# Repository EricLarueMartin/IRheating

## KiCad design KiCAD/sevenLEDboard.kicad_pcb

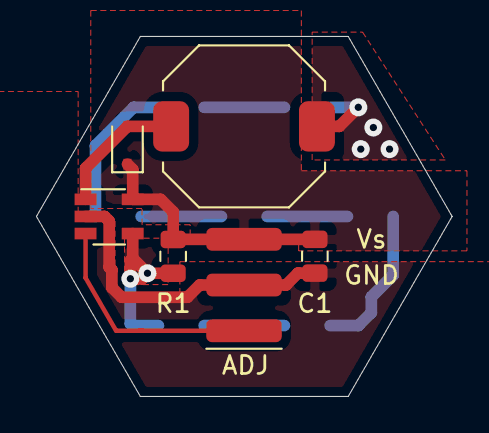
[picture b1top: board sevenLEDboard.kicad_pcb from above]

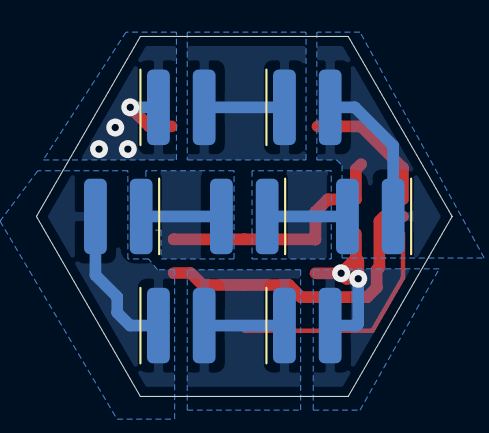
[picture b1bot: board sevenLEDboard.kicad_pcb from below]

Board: 2 copper layers, 23.1 x 20.0 mm, 13 parts (7 on the bottom side), 12 nets.

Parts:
C1: 10uF; C_0805_2012Metric
D1, D2, D3, D4, D5, D6, D7: SFH 4550; 91601-302LF
D8: D_Schottky; D_SOD-323
J1: Conn_01x03_Male; 91601-303LF
L1: 68uH; CDRH8D58
R1: 1; R_0805_2012Metric
U1: ZXLD1350; TSOT-23-5

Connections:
GND: C1.2, J1.2, U1.2
unnamed: D1.1, D2.2
unnamed: D1.2, R1.1, U1.4
unnamed: D2.1, D3.2
unnamed: D3.1, D4.2
unnamed: D4.1, D5.2
unnamed: D5.1, D6.2
unnamed: D6.1, D7.2
unnamed: D7.1, L1.1
unnamed: D8.2, L1.2, U1.1
unnamed: J1.1, U1.3
VS: C1.1, D8.1, J1.3, R1.2, U1.5

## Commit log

2021-11-10 Data sheets and model for some selected components.
2021-11-11 Design and layout of 7 LED board.
2021-11-11 Updated board. Draft for review before PCB submission.
2021-11-12 Final changes with fabrication outputs.
2021-11-12 Created production 7 LED board with ZXLD1350 DC-DC bucking regulator.
2021-11-15 holder design
2021-11-15 Threaded hole
2021-11-15 Ignored old versions in inventor.
2021-11-17 Modified KF50 feedthrough and cleaned up old LED driver versions.
2021-11-18 Changed print file
2021-11-19 Changing angle by 30deg working copy.
2021-11-29 Modified bracket and added stand.
2021-12-01 Fixed array bracket mounting to tilt on axis.
2021-12-03 Added vertical mounting tabs.
2021-12-03 Removed two extreme arrays for vertical mounting.
2021-12-06 Update stl
2021-12-08 modified for vertical
2022-02-02 Fixed partial pdf.
